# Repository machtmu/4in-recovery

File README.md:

# Recovery Module Repository

---

<div align="center">
  <div>

    <p><em>3D Render</em></p>
  </div>
  <br>

  <div>
    <br>
    <p><em>Schematic</em></p>
  </div>
  <br>
  
  <div>
    
    <br>
    <em>Footprint</em>
  </div>
</div>

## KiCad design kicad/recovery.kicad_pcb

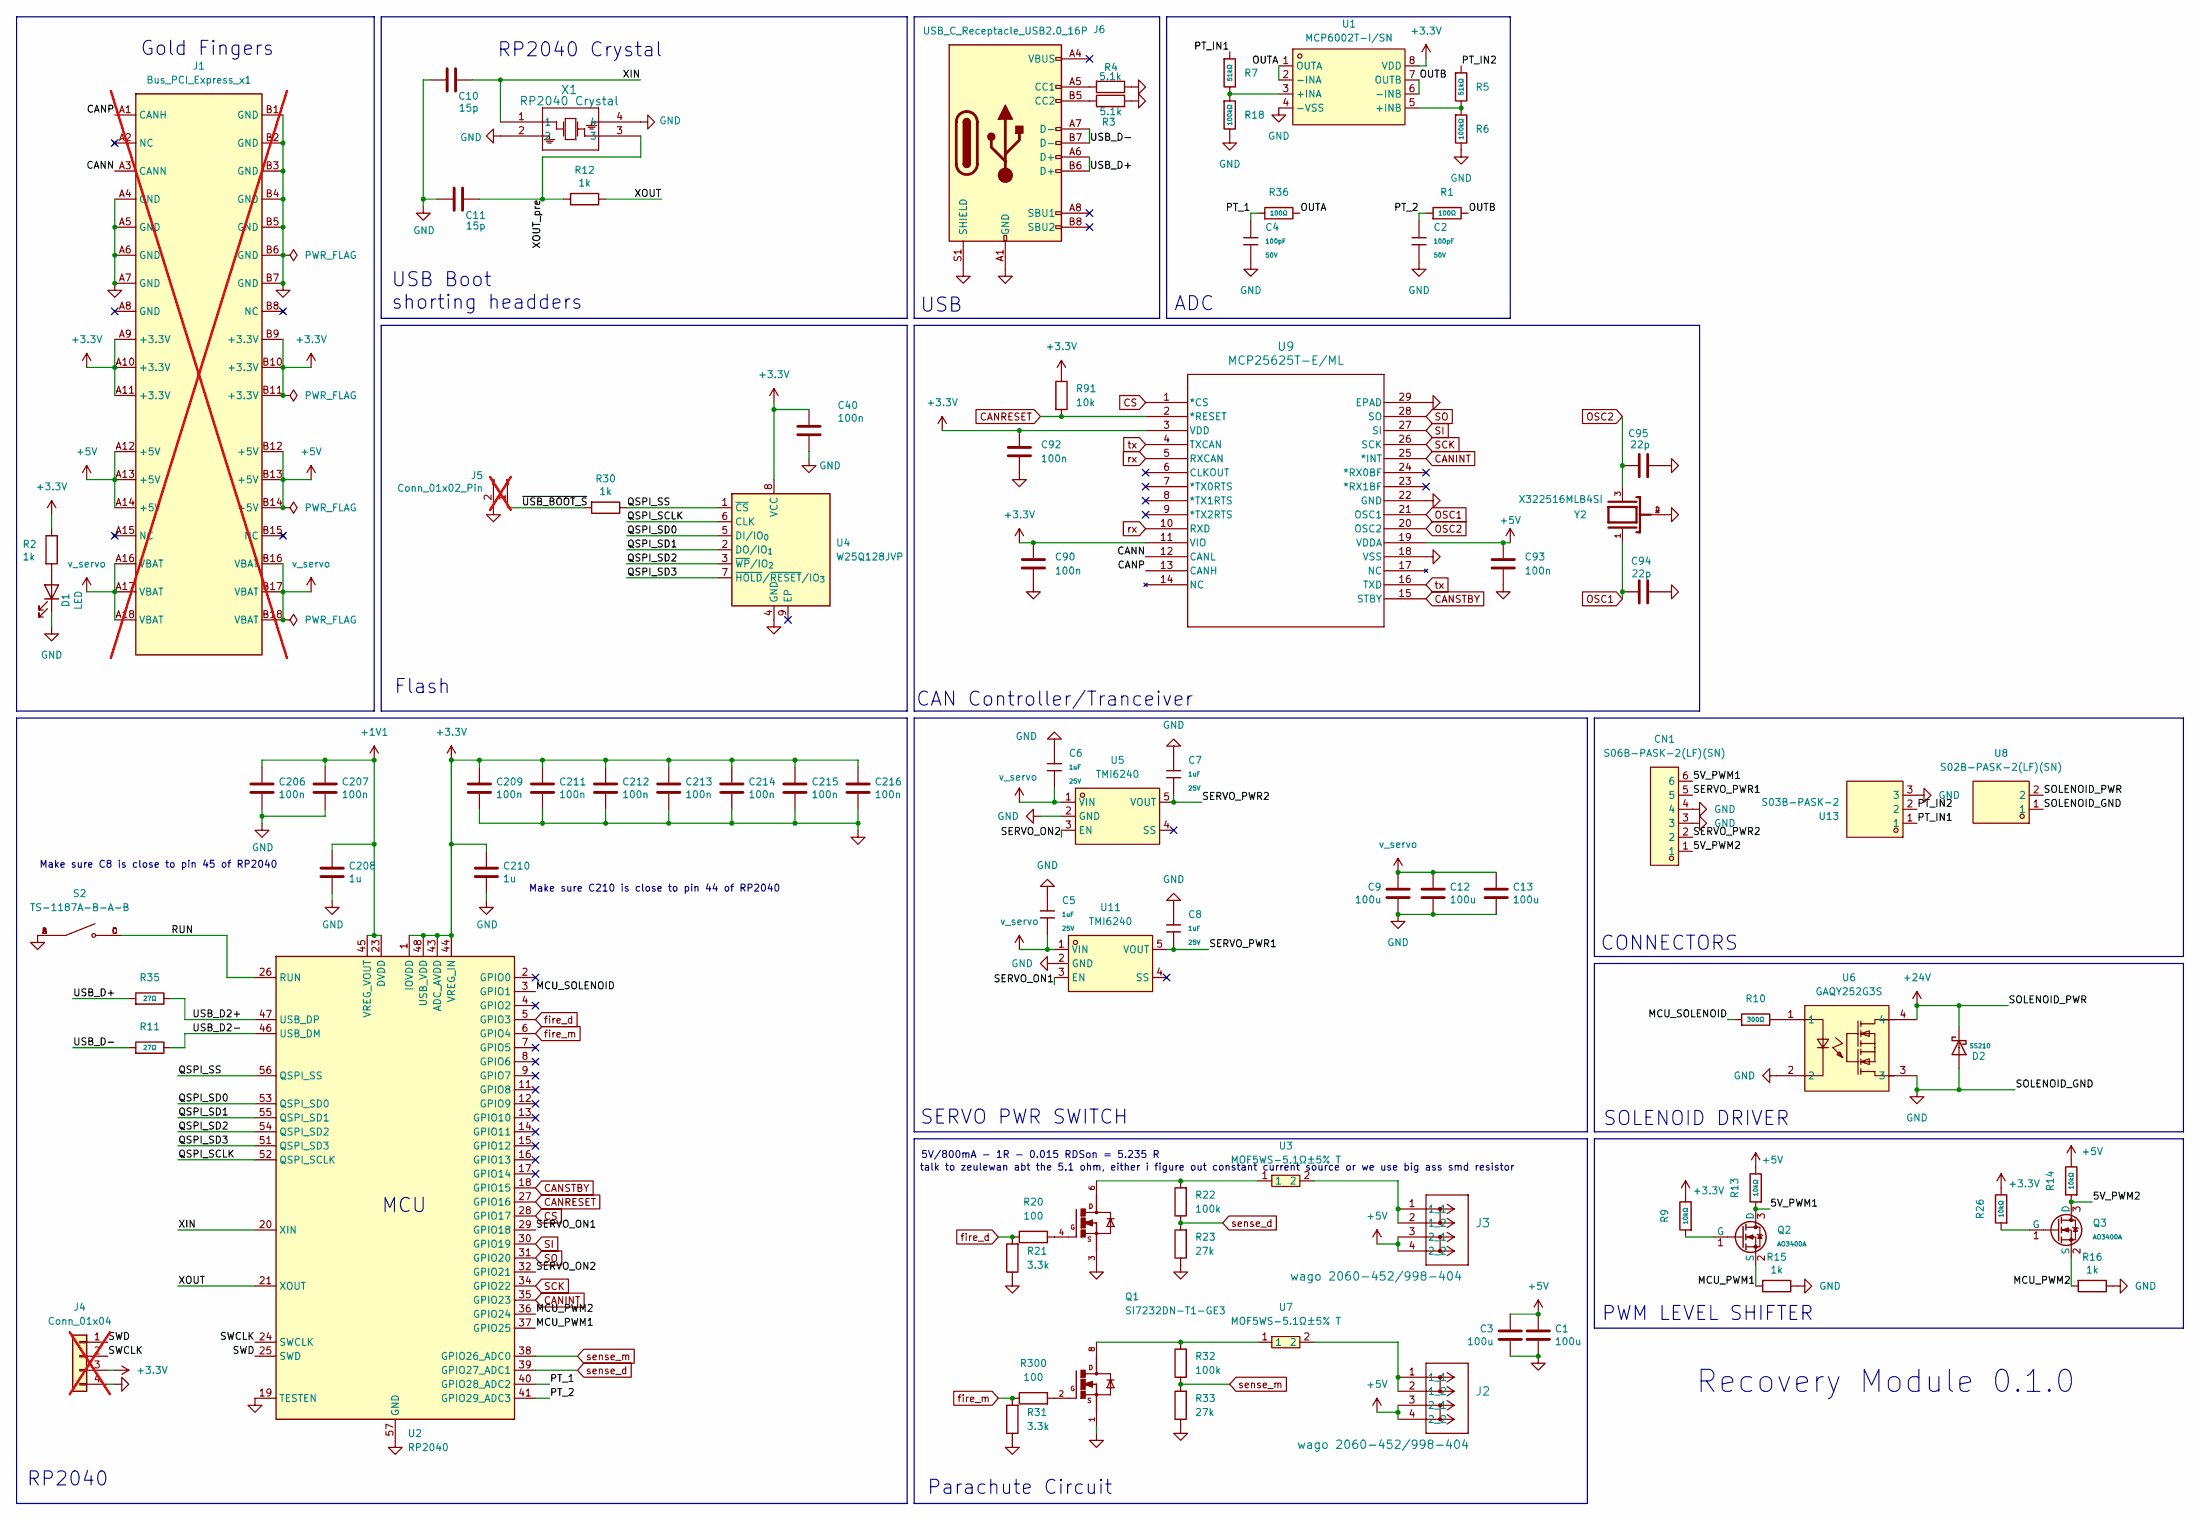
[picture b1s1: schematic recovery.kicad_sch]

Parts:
C1, C3, C9, C12, C13: 100u; C_1210_3225Metric; LCSC PN C23742
C2, C4: 100pF; C_0603; Voltage Rated 50V; Tolerance ±5%; Part CL10C101JB8NNNC; LCSC C14858
C5, C6, C7, C8: 1uF; C_0402; Voltage Rated 25V; Tolerance ±10%; Part CL05A105KA5NQNC; LCSC C52923
C10, C11: 15p; C_0402_1005Metric; LCSC PN C1548
C40, C90, C92, C93, C206, C207, C209, C211, C212, C213, C214, C215, C216: 100n; C_0402_1005Metric; LCSC PN C307331
C94, C95: 22p; C_0402_1005Metric; LCSC PN C1555
C208, C210: 1u; C_0402_1005Metric; LCSC PN C52923
CN1: S06B-PASK-2(LF)(SN); CONN-TH_6P-P2.00_S06B-PASK-2-LF-SN; LCSC Part C495643
D1: LED; LED_0603_1608Metric; LCSC PN C2286
D2: SS210; D_SMA; Forward Voltage (Vf@If) 850mV@2A; Reverse Voltage (Vr) 100V; Part SS210; LCSC C14996
J1: Bus_PCI_Express_x1; PCIeX1; not fitted
J2, J3: wago 2060-452/998-404; wago-2060-452_998-404; LCSC PN C2765055
J4: Conn_01x04; PinHeader_1x04_P2.54mm_Vertical; not fitted
J5: Conn_01x02_Pin; PinHeader_1x02_P2.54mm_Vertical; not fitted
J6: USB_C_Receptacle_USB2.0_16P; USB_C_Receptacle_Palconn_UTC16-G; LCSC PN C2765186
Q1: SI7232DN-T1-GE3; LCSC PN C144854
Q2, Q3: AO3400A; Q_SOT-23; Part AO3400A; LCSC C20917
R1, R36: 100Ω; R_0603; Overload Voltage (Max) 75V; Tolerance ±1%; Part 0603WAF1000T5E; LCSC C22775
R2, R12, R15, R16, R30: 1k; R_0402_1005Metric; LCSC PN C11702
R3, R4: 5.1k; R_0402_1005Metric; LCSC PN C25905
R5, R7: 51kΩ; R_0603; Overload Voltage (Max) 75V; Tolerance ±1%; Part 0603WAF5102T5E; LCSC C23196
R6, R18: 100kΩ; R_0603; Overload Voltage (Max) 75V; Tolerance ±1%; Part 0603WAF1003T5E; LCSC C25803
R9, R13, R14, R26: 10kΩ; R_0402; Overload Voltage (Max) 50V; Tolerance ±1%; Part 0402WGF1002TCE; LCSC C25744
R10: 300Ω; R_0603; Overload Voltage (Max) 75V; Tolerance ±1%; Part 0603WAF3000T5E; LCSC C23025
R11, R35: 27Ω; R_0603; Overload Voltage (Max) 75V; Tolerance ±1%; Part 0603WAF270JT5E; LCSC C25190
R20, R300: 100; R_0402_1005Metric; LCSC PN C25076
R21, R31: 3.3k; R_0402_1005Metric; LCSC PN C25890
R22, R32: 100k; R_0402_1005Metric; LCSC PN C25741
R23, R33: 27k; R_0402_1005Metric; LCSC PN C25551
R91: 10k; R_0402_1005Metric; LCSC PN C25744
S2: TS-1187A-B-A-B; Manufacturer PN TS-1187A-B-A-B; LCSC PN C318884
U1: MCP6002T-I/SN; SOIC-8_L4.9-W3.9-P1.27-LS6.0-BL; LCSC Part C7377
U2: RP2040; QFN-56-1EP_7x7mm_P0.4mm_EP3.2x3.2mm; LCSC PN C2040
U3, U7: MOF5WS-5.1Ω±5% T; RES-TH_BD6.0-L17.5-P21.50-D0.7; LCSC Part C121946
U4: W25Q128JVP; WSON-8-1EP_6x5mm_P1.27mm_EP3.4x4.3mm; LCSC PN C190862
U5, U11: TMI6240; SOT-23-5_L2.9-W1.6-P0.95-LS2.8-BL; LCSC Part C2979914
U6: GAQY252G3S; SOP-4_L4.3-W4.4-P2.54-LS7.0-BL; LCSC Part C7435106
U8: S02B-PASK-2(LF)(SN); CONN-TH_S02B-PASK-2-LF-SN; LCSC Part C265094
U9: MCP25625T-E/ML; QFN28_6X6MC_MCH; LCSC PN C191253
U13: S03B-PASK-2; CONN-TH_S03B-PASK-2-LF-SN; LCSC Part C265095
X1: RP2040 Crystal; ABM8-272-T3_ABR; Manufacturer PN ABM8-272-T3_ABR; LCSC PN C20625731
Y2: X322516MLB4SI; LCSC PN C12668

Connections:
+1V1: C206.1, C207.1, C208.1, U2.23 (DVDD), U2.45 (VREG_VOUT), U2.50 (DVDD)
+3.3V: C40.1, C90.1, C92.1, C209.1, C210.1, C211.1, C212.1, C213.1, C214.1, C215.1, C216.1, J1.A9 (+3.3V), J1.A10 (+3.3V), J1.A11 (+3.3V), J1.B9 (+3.3V), J1.B10 (+3.3V), J1.B11 (+3.3V), J4.3, R2.1, R9.2, R26.2, R91.1, U1.8 (VDD), U2.1 (IOVDD), U2.10 (IOVDD), U2.22 (IOVDD), U2.33 (IOVDD), U2.42 (IOVDD), U2.43 (ADC_AVDD), U2.44 (VREG_IN), U2.48 (USB_VDD), U2.49 (IOVDD), U4.8 (VCC), U9.3 (VDD), U9.11 (VIO)
+5V: C1.1, C3.1, C93.1, J1.A12 (+5V), J1.A13 (+5V), J1.A14 (+5V), J1.B12 (+5V), J1.B13 (+5V), J1.B14 (+5V), J2.3 (2_1), J2.4 (2_2), J3.3 (2_1), J3.4 (2_2), R13.2, R14.2, U9.19 (VDDA); also elsewhere on the board
+24V: D2.1, U6.4, U8.2
/5V_PWM1: CN1.6, Q2.3 (D), R13.1; also elsewhere on the board
/5V_PWM2: CN1.1, Q3.3 (D), R14.1
/CANN: J1.A3 (CANN), U9.12 (CANL)
/CANP: J1.A1 (CANH), U9.13 (CANH)
/MCU_PWM1: Q2.2 (S), R15.2, U2.37 (GPIO25)
/MCU_PWM2: Q3.2 (S), R16.2, U2.36 (GPIO24)
/MCU_SOLENOID: R10.1, U2.3 (GPIO1)
/OUTA: R36.2, U1.1 (OUTA), U1.2 (-INA)
/OUTB: R1.2, U1.6 (-INB), U1.7 (OUTB)
/PT_1: C4.1, R36.1, U2.40 (GPIO28_ADC2)
/PT_2: C2.1, R1.1, U2.41 (GPIO29_ADC3)
/PT_IN1: R7.1, U13.1
/PT_IN2: R5.1, U13.2
/QSPI_SCLK: U2.52 (QSPI_SCLK), U4.6 (CLK)
/QSPI_SD0: U2.53 (QSPI_SD0), U4.5 (DI/IO_{0})
/QSPI_SD1: U2.55 (QSPI_SD1), U4.2 (DO/IO_{1})
/QSPI_SD2: U2.54 (QSPI_SD2), U4.3 (~WP/IO_{2})
/QSPI_SD3: U2.51 (QSPI_SD3), U4.7 (~HOLD/~RESET/IO_{3})
/QSPI_SS: R30.1, U2.56 (QSPI_SS), U4.1 (~CS)
/RUN: S2.C, S2.D, U2.26 (RUN)
/SERVO_ON1: U2.29 (GPIO18), U11.3 (EN)
/SERVO_ON2: U2.32 (GPIO21), U5.3 (EN)
/SERVO_PWR1: C8.2, CN1.5, U11.5 (VOUT); also elsewhere on the board
/SERVO_PWR2: C7.2, CN1.2, U5.5 (VOUT); also elsewhere on the board
/SWCLK: J4.2, U2.24 (SWCLK)
/SWD: J4.1, U2.25 (SWD)
/USB_D2+: R35.2, U2.47 (USB_DP)
/USB_D2-: R11.2, U2.46 (USB_DM)
/USB_D+: J6.A6 (D+), J6.B6 (D+), R35.1
/USB_D-: J6.A7 (D-), J6.B7 (D-), R11.1
/XIN: C10.1, U2.20 (XIN), X1.1
/XOUT: R12.1, U2.21 (XOUT)
/XOUT_pre: C11.1, R12.2, X1.3
/~USB_BOOT_S: J5.1, R30.2
CANINT: U2.35 (GPIO23), U9.25 (*INT)
CANRESET: R91.2, U2.27 (GPIO16), U9.2 (*RESET)
CANSTBY: U2.18 (GPIO15), U9.15 (STBY)
CS: U2.28 (GPIO17), U9.1 (*CS)
GND: C1.2, C2.2, C3.2, C4.2, C5.1, C6.1, C7.1, C8.1, C9.2, C10.2, C11.2, C12.2, C13.2, C40.2, C90.2, C92.2, C93.2, C94.2, C95.2, C206.2, C207.2, C208.2, C209.2, C210.2, C211.2, C212.2, C213.2, C214.2, C215.2, C216.2, CN1.3, CN1.4, D1.1 (K), D2.2, J1.A4 (GND), J1.A5 (GND), J1.A6 (GND), J1.A7 (GND), J1.B1 (GND), J1.B2 (GND), J1.B3 (GND), J1.B4 (GND), J1.B5 (GND), J1.B6 (GND), J1.B7 (GND), J4.4, J5.2, J6.A1 (GND), J6.A12 (GND), J6.B1 (GND), J6.B12 (GND), J6.S1 (SHIELD), Q1.1, Q1.3, R3.2, R4.1, R6.2, R15.1, R16.1, R18.2, R21.1, R23.1, R31.1, R33.1, S2.A, S2.B, U1.4 (-VSS), U2.19 (TESTEN), U2.57 (GND), U4.4 (GND), U5.2 (GND), U6.2, U6.3, U8.1, U9.18 (VSS), U9.22 (GND), U9.29 (EPAD), U11.2 (GND), U13.3, X1.2, X1.4, Y2.2, Y2.4; also elsewhere on the board
unnamed: D1.2 (A), R2.2
unnamed: J2.1 (1_1), J2.2 (1_2), U7.2
unnamed: J3.1 (1_1), J3.2 (1_2), U3.2
unnamed: J6.A5 (CC1), R4.2
unnamed: J6.B5 (CC2), R3.1
unnamed: Q1.2, R300.2
unnamed: Q1.4, R20.2
unnamed: Q1.5, Q1.6, R22.2, U3.1
unnamed: Q1.7, Q1.8, R32.2, U7.1
unnamed: Q2.1 (G), R9.1
unnamed: Q3.1 (G), R26.1
unnamed: R10.2, U6.1
unnamed: R7.2, R18.1, U1.3 (+INA)
unnamed 56: R5.2, R6.1, U1.5 (+INB); also elsewhere on the board
OSC1: C94.1, U9.21 (OSC1), Y2.1
OSC2: C95.1, U9.20 (OSC2), Y2.3
SCK: U2.34 (GPIO22), U9.26 (SCK)
SI: U2.30 (GPIO19), U9.27 (SI)
SO: U2.31 (GPIO20), U9.28 (SO)
fire_d: R20.1, R21.2, U2.5 (GPIO3)
fire_m: R31.2, R300.1, U2.6 (GPIO4)
rx: U9.5 (RXCAN), U9.10 (RXD)
sense_d: R22.1, R23.2, U2.39 (GPIO27_ADC1)
sense_m: R32.1, R33.2, U2.38 (GPIO26_ADC0)
tx: U9.4 (TXCAN), U9.16 (TXD)
v_servo: C5.2, C6.2, C9.1, C12.1, C13.1, J1.A16 (VBAT), J1.A17 (VBAT), J1.A18 (VBAT), J1.B16 (VBAT), J1.B17 (VBAT), J1.B18 (VBAT), U5.1 (VIN), U11.1 (VIN); also elsewhere on the board

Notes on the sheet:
Make sure C210 is close to pin 44 of RP2040
Make sure C8 is close to pin 45 of RP2040
RP2040 Crystal
5V/800mA - 1R - 0.015 RDSon = 5.235 R
ADC
USB
CONNECTORS
PWM LEVEL SHIFTER
SERVO PWR SWITCH
talk to zeulewan abt the 5.1 ohm, either i figure out constant current source or we use big ass smd resistor
USB Boot shorting headders
Parachute Circuit
SOLENOID DRIVER
Recovery Module 0.1.0
Gold Fingers
RP2040
MCU
CAN Controller/Tranceiver
Flash

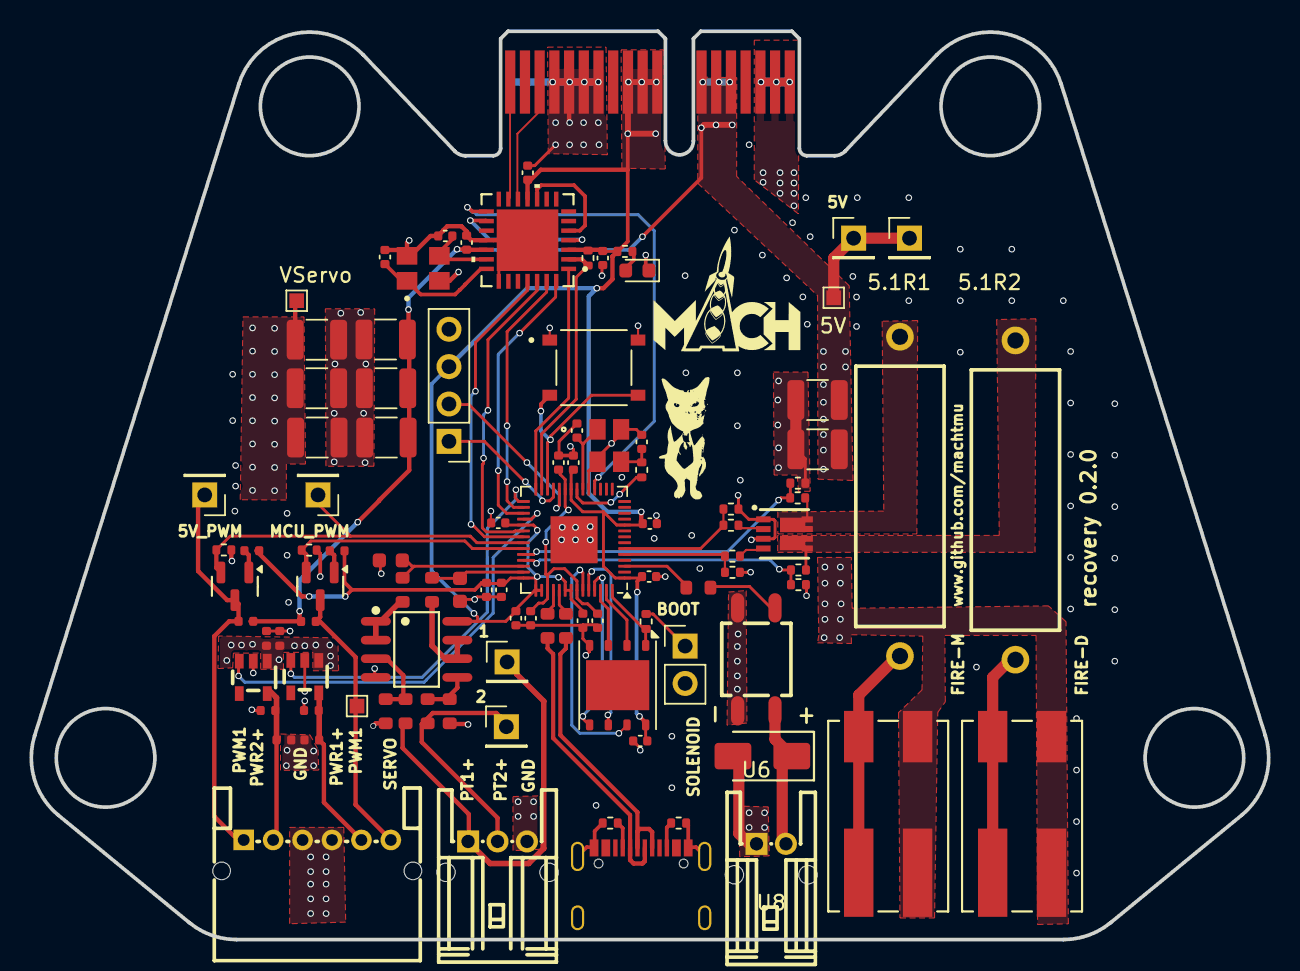
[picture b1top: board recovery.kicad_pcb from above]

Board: 4 copper layers, 84.1 x 61.7 mm, 93 parts (1 on the bottom side), 69 nets.

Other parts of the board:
5V: TestPoint_Pad_1.0x1.0mm
C5#2, C5#3, C6#2, C12#2: 100u; C_1210_3225Metric
C29, C30: 100nF; C_0402
PWM1: TestPoint_Pad_1.0x1.0mm
R17: 33kΩ; R_0603
VServo: TestPoint_Pad_1.0x1.0mm

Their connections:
+5V: 5V.1, C5#2.1, C5#3.1, C6#2.1; also elsewhere on the board
/5V_PWM1: PWM1.1; also elsewhere on the board
/SERVO_PWR1: C29.1; also elsewhere on the board
/SERVO_PWR2: C30.1; also elsewhere on the board
GND: C5#2.2, C5#3.2, C6#2.2, C12#2.2, C29.2, C30.2, R17.2; also elsewhere on the board
unnamed 56: R17.1; also elsewhere on the board
v_servo: C12#2.1, VServo.1; also elsewhere on the board

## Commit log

2025-01-26 Update images
2025-01-26 init
2025-03-08 export step file
2025-04-03 update libraries
2025-04-03 add wago connectors, update components with chips from new library
2025-04-04 update PCB
2025-04-04 update step file
2025-05-15 rename symbol and footprint editor
2025-05-15 add dual N channel mosfet symbol and footprint
2025-05-16 add proper net names to recovery section
2025-05-16 begin fet routing
2025-05-17 fix outline
2025-05-18 update PCIe footprint
2025-05-18 finish routing
2025-05-18 final gerber export
2025-09-18 Feat: Added load switch, PWM level shifters, ADC and buffer circuitry, connectors and solenod driver to schematic
    Fix: Reorganized schematic to be readable, modified parachute circuit to utilize 5V.
2025-10-01 feat: overhauled recovery board: added servos, solenoids, PWM-level shifters and firing circuit to layout
2025-10-01 fix: cleaned file directory
2025-10-18 Feat: Completed layout, modified divider network for 5V PT operation
2025-10-28 fix: Reviewed components tolerances and BOM for version alpha
2025-11-19 Change workflow reference for exporting KiCad images
